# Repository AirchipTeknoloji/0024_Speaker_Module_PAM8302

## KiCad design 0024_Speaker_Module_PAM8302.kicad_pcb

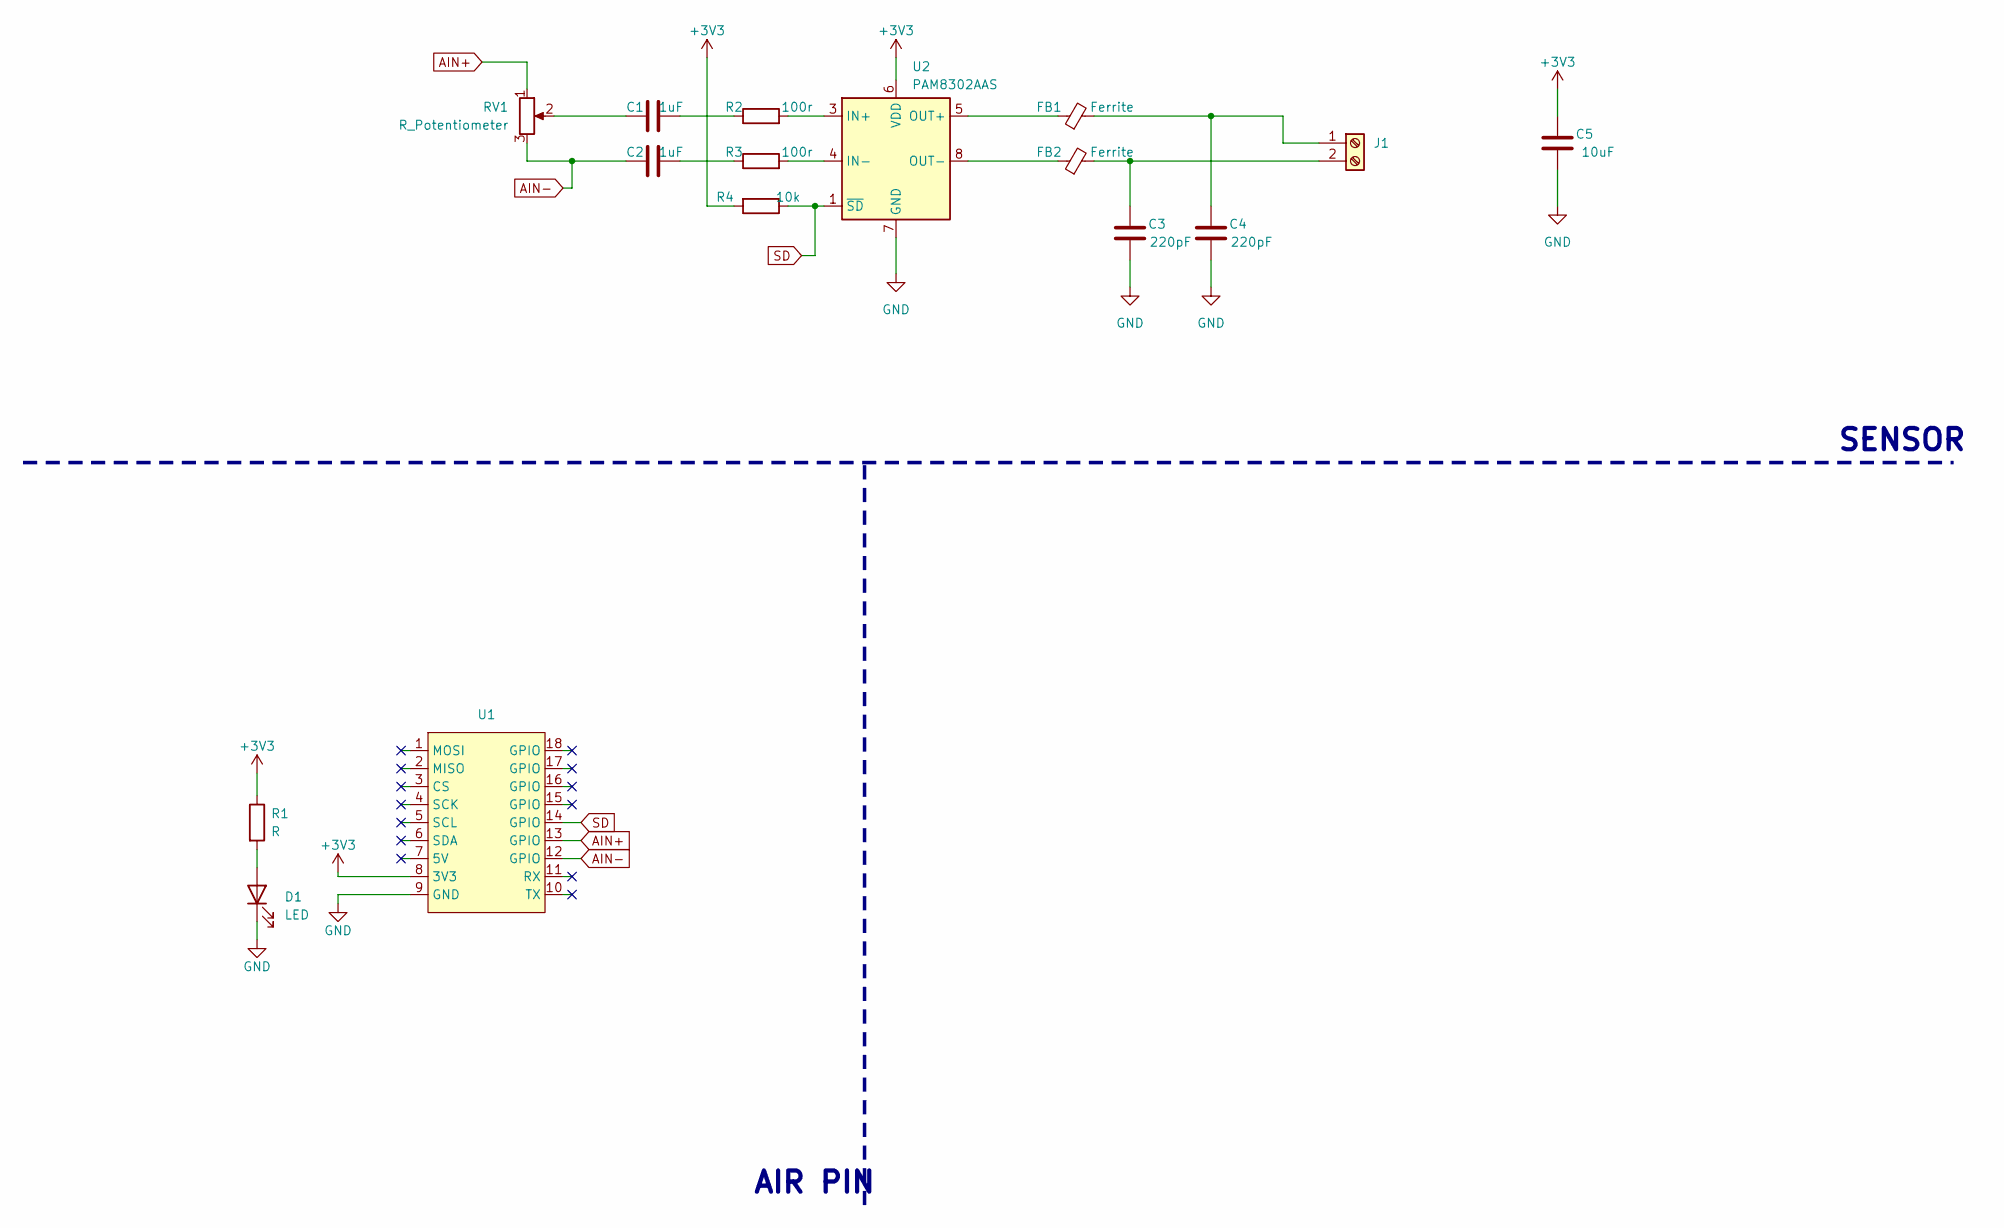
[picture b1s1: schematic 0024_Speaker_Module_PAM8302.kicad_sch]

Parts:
C1, C2: 1uF; C_0805_2012Metric
C3, C4: 220pF; C_0805_2012Metric
C5: 10uF; C_0603_1608Metric
D1: LED; LED_0805_2012Metric
FB1, FB2: Ferrite; L_0805_2012Metric
J1: Screw_Terminal_01x02; TerminalBlock_Phoenix_MKDS-1,5-2-5.08_1x02_P5.08mm_Horizont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
R1: R; R_0805_2012Metric
R2, R3: 100r; R_0805_2012Metric
R4: 10k; R_0805_2012Metric
RV1: R_Potentiometer; 3362P_1
U1: air_module
U2: PAM8302AAS; MSOP-8_3x3mm_P0.65mm

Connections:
+3V3: C5.2, R1.1, R4.2, U1.8 (3V3), U2.6 (VDD)
AIN+: RV1.1, U1.13 (GPIO); also elsewhere on the board
AIN-: C2.1, RV1.3, U1.12 (GPIO); also elsewhere on the board
GND: C3.1, C4.1, C5.1, D1.1 (K), U1.9 (GND), U2.7 (GND)
unnamed 4: C1.1, RV1.2; also elsewhere on the board
unnamed: C1.2, R2.1
unnamed: C2.2, R3.1
unnamed: D1.2 (A), R1.2
unnamed: C4.2, FB1.2, J1.1
unnamed: C3.2, FB2.2, J1.2
unnamed: R2.2, U2.3 (IN+)
unnamed: R3.2, U2.4 (IN-)
unnamed: FB1.1, U2.5 (OUT+)
unnamed: FB2.1, U2.8 (OUT-)
SD: R4.1, U1.14 (GPIO), U2.1 (~SD)

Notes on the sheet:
AIR PIN
SENSOR

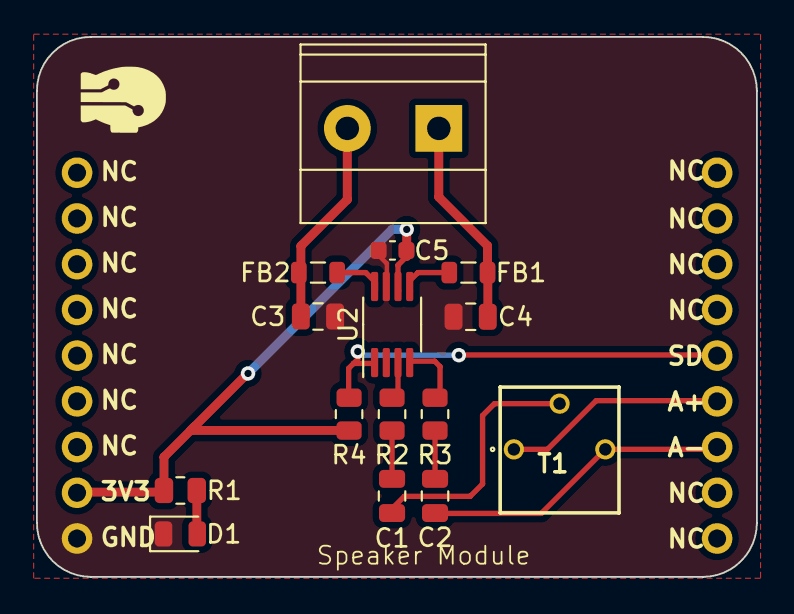
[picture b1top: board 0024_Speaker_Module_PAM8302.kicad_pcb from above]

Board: 2 copper layers, 40.0 x 30.0 mm, 16 parts (0 on the bottom side), 15 nets.

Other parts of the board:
T1: R_Potentiometer; 3362P_1

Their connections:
AIN+: T1.1; also elsewhere on the board
AIN-: T1.3; also elsewhere on the board
unnamed 4: T1.2; also elsewhere on the board
